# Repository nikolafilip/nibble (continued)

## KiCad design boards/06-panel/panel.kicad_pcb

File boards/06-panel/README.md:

# Board 06: front panel

The test fixture and the face of the machine. 80 transistors, 56 LEDs, 72 resistors.

- **Level switches** (four DIP-8): A3..A0, B3..B0, and the 24 control lines. A closed switch connects the line to +5 V through 10k, so a switch left on can never fight a board that pulls the line low; it only supplies a 1 where nothing else drives.
- **Data switches** (DIP-4): the input port. A closed switch is a 1; while `INP` is high the four bits are driven onto the bus through the usual NAND and open-drain transistor, which is how the IN instruction reads them. To force the bus by hand, close the INP switch too.
- **CLK and RST buttons**: RC debounce, an NMOS Schmitt trigger (two inverters, 1 Meg feedback), 10k and a diode onto the line. One press = one clean edge at every threshold corner (simulated with contact bounce). The clock board can drive the same lines later.
- **1 Meg pull-down** on every switched or observed line, so a line reads 0 when no board drives it.
- **An LED on every line**: 52 bus lines directly, plus the four data bits through inverters so the LED shows the data, not the active-low wire.

First test with hub + panel + ALU: set A, B, SUB, EO on the switches; read the result on the data LEDs and CF/ZF.
Generated by `sim/build_panel.py`. ERC clean; export simulated (`sim/out/panel_sim.cir`).

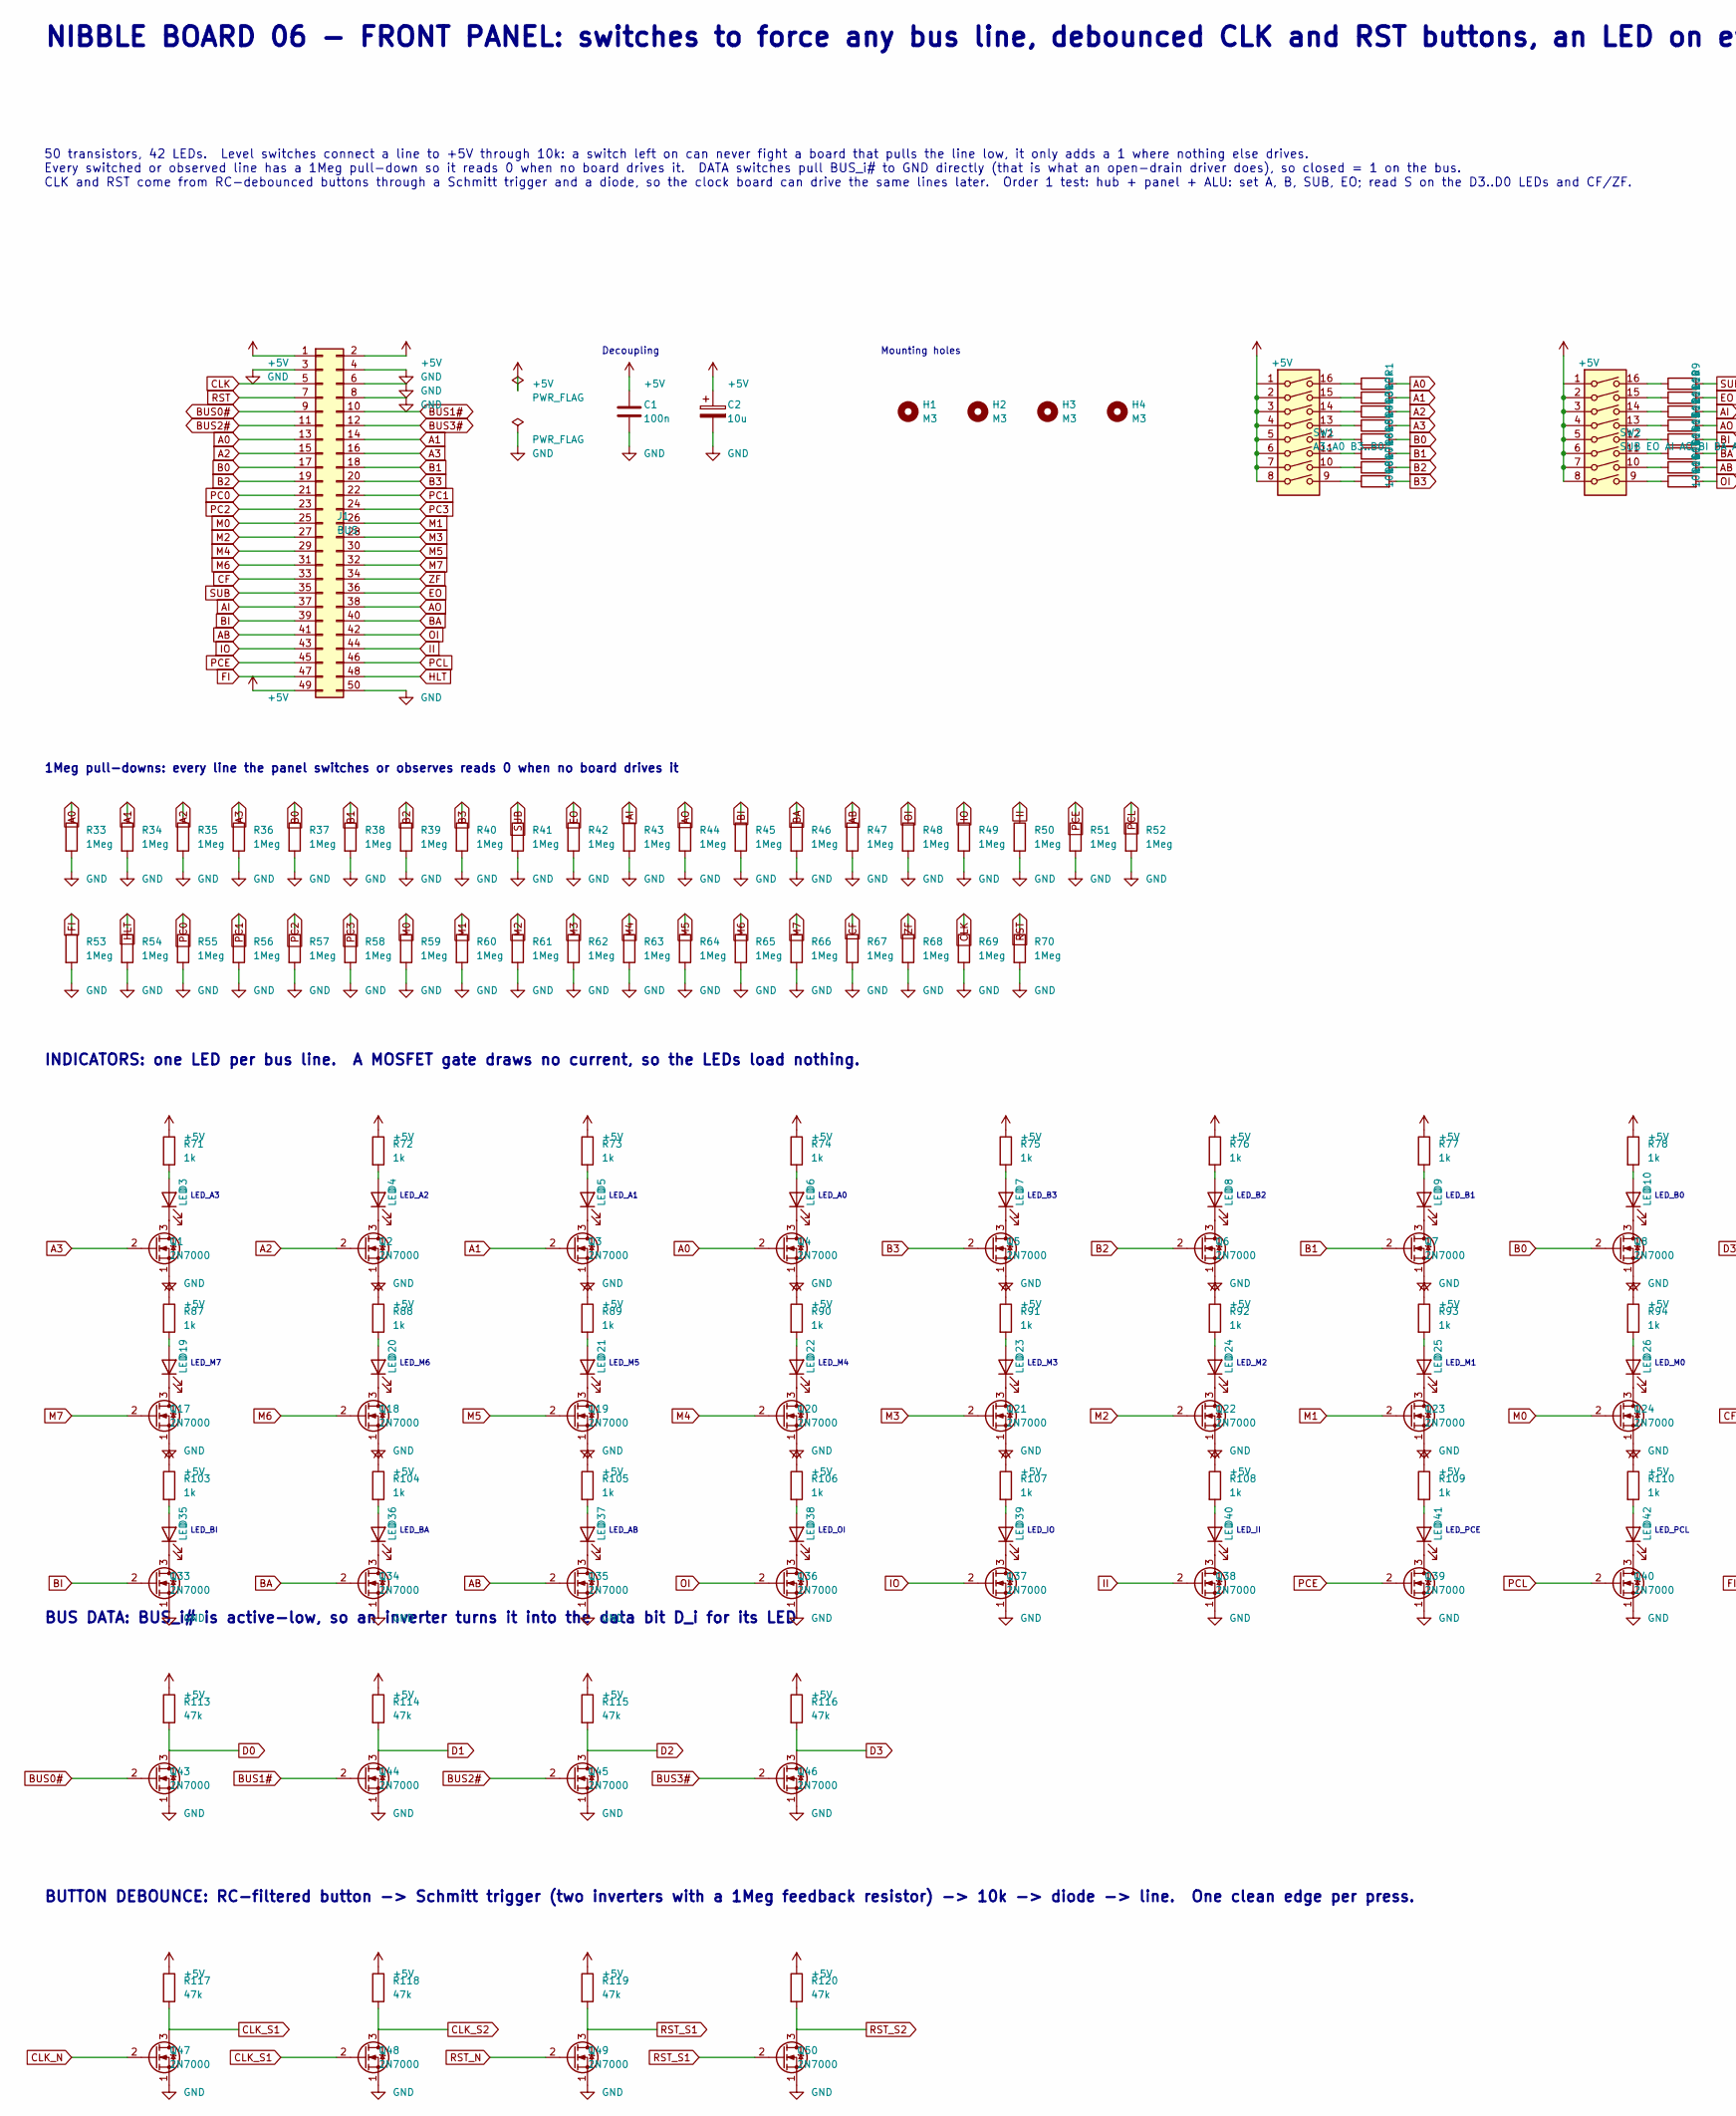
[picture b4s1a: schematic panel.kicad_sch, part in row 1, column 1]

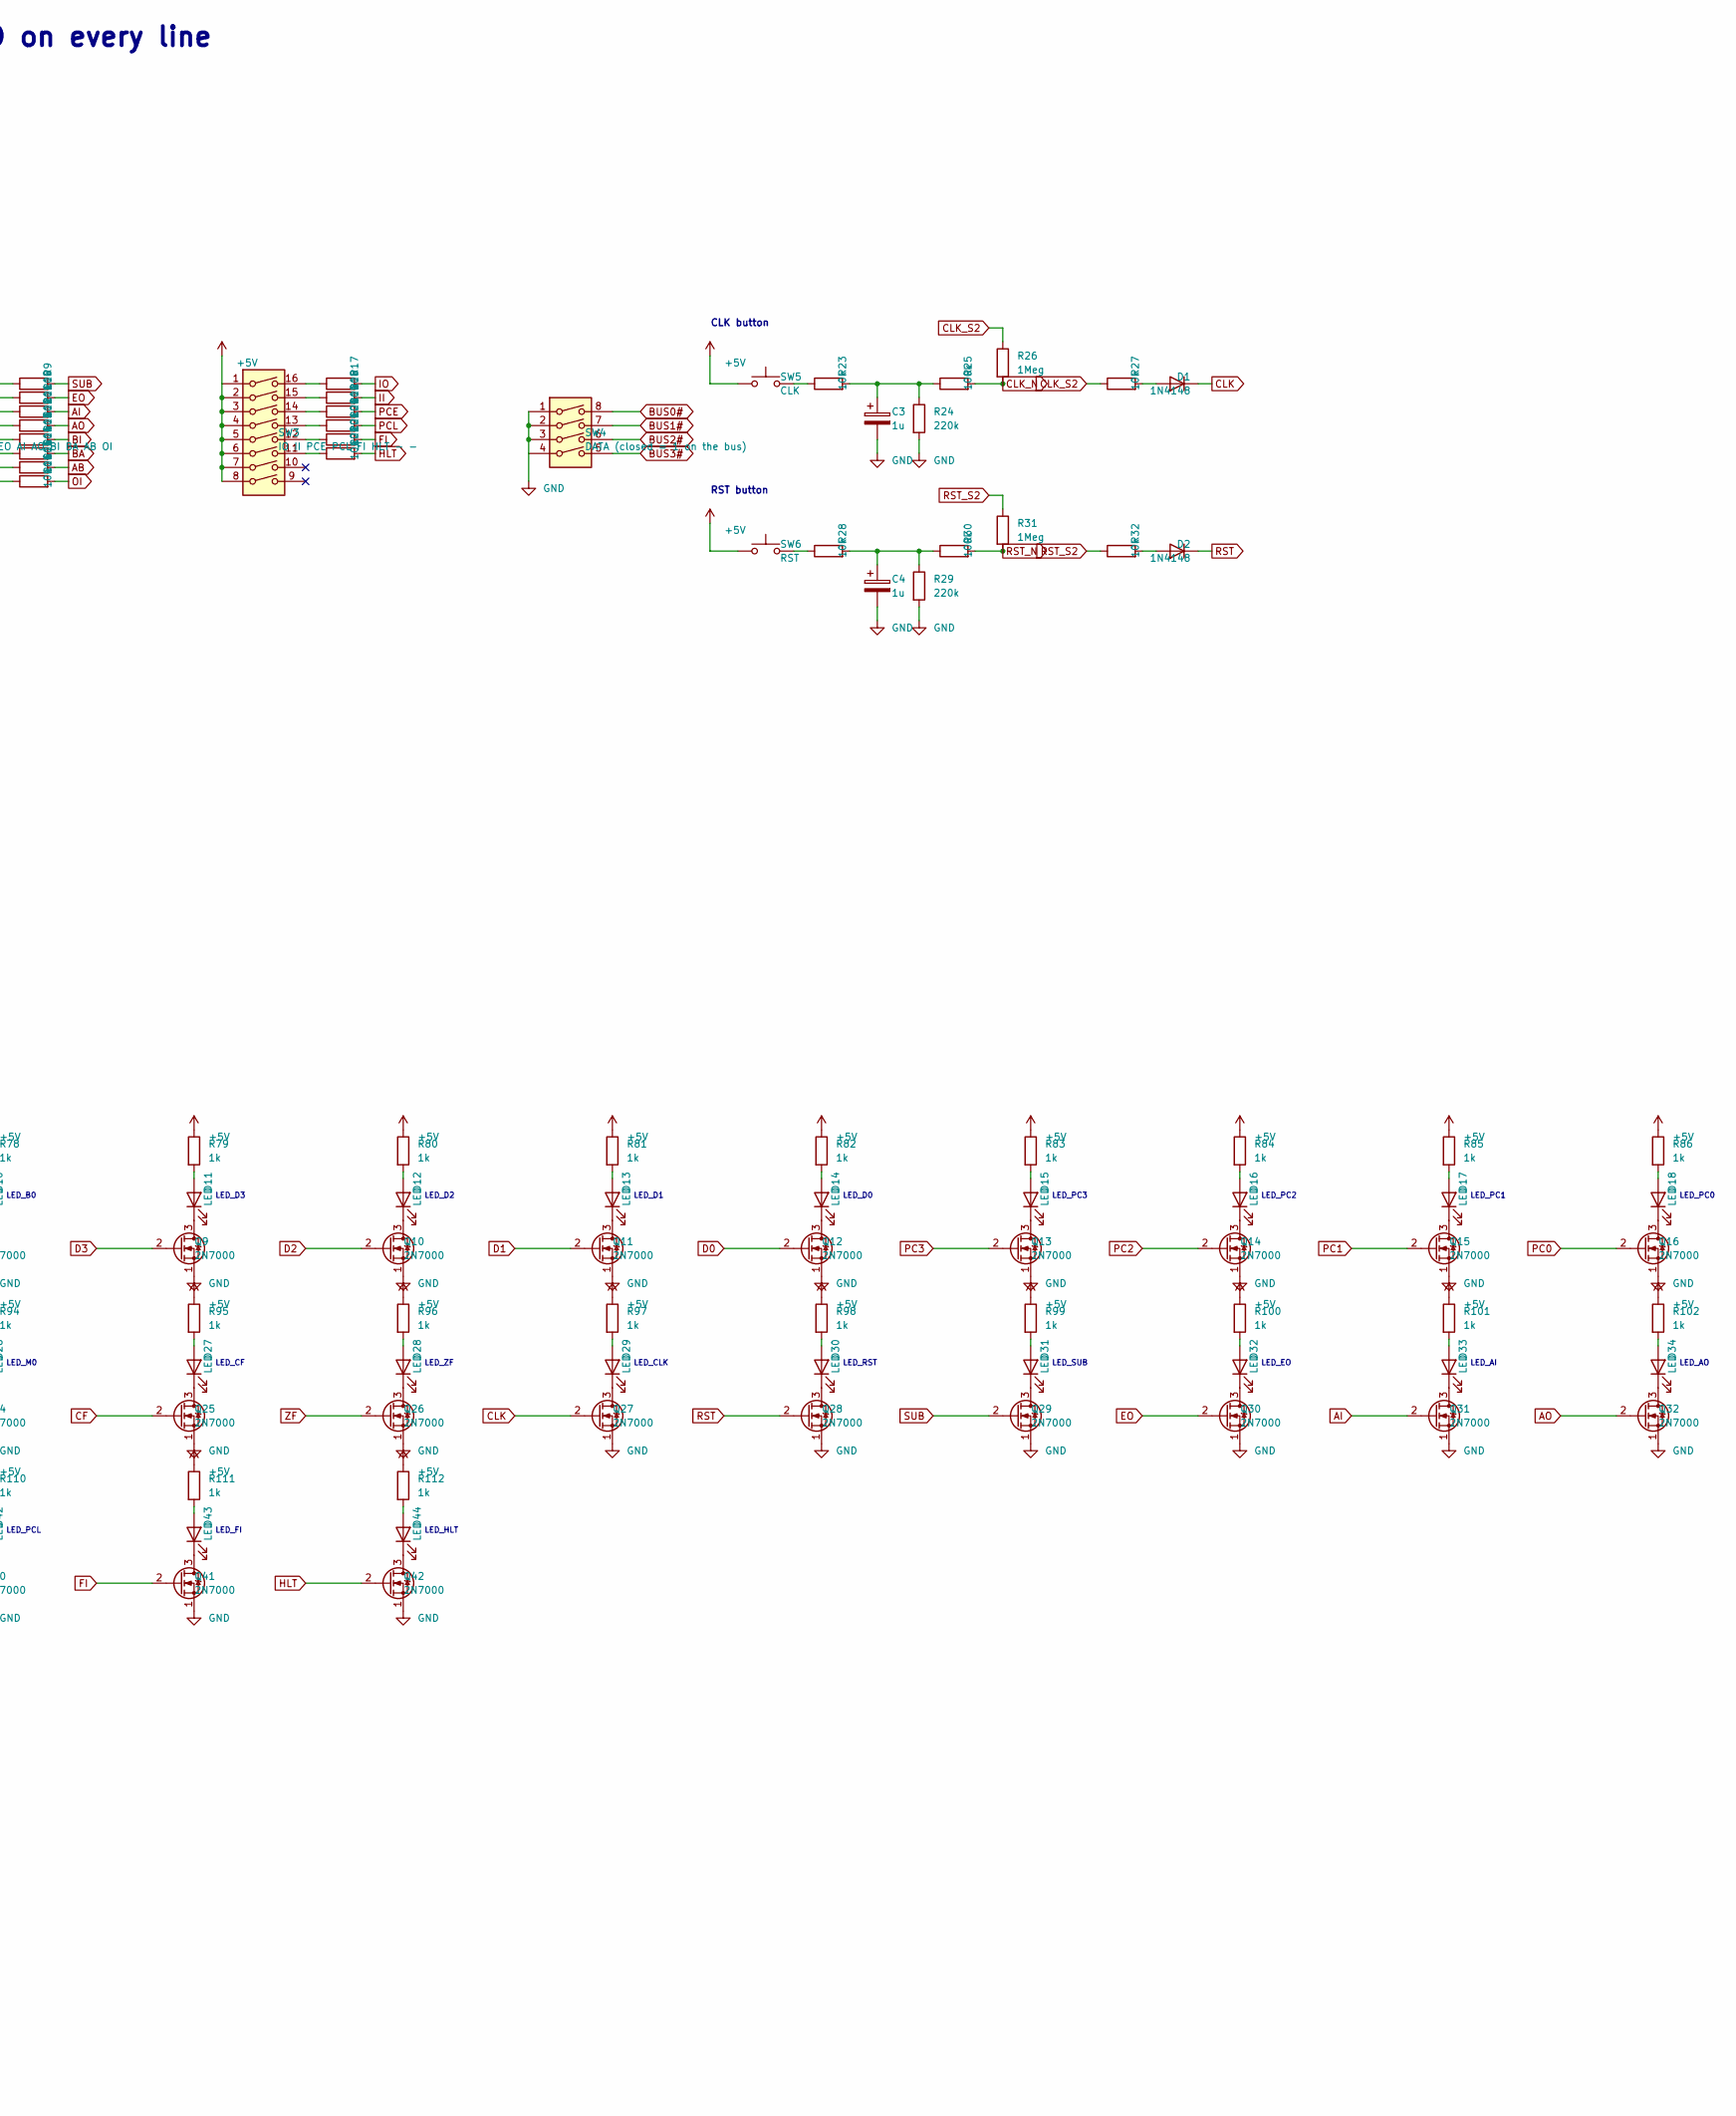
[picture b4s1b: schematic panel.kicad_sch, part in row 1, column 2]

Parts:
C1: 100n; C_Disc_D5.0mm_W2.5mm_P2.50mm
C2: 10u; CP_Radial_D5.0mm_P2.00mm
C3, C4: 1u; CP_Radial_D5.0mm_P2.00mm
D1, D2: 1N4148; D_DO-35_SOD27_P7.62mm_Horizontal
D3, D4, D5, D6, D7, D8, D9, D10, D11, D12, D13, D14, D15, D16, D17, D18, D19, D20, D21, D22, D23, D24, D25, D26, D27, D28, D29, D30, D31, D32, D33, D34, D35, D36, D37, D38, D39, D40, D41, D42, D43, D44: LED; LED_D3.0mm
H1, H2, H3, H4: M3; MountingHole_3.2mm_M3_Pad
J1: BUS; IDC-Header_2x25_P2.54mm_Vertical
Q1, Q2, Q3, Q4, Q5, Q6, Q7, Q8, Q9, Q10, Q11, Q12, Q13, Q14, Q15, Q16, Q17, Q18, Q19, Q20, Q21, Q22, Q23, Q24, Q25, Q26, Q27, Q28, Q29, Q30, Q31, Q32, Q33, Q34, Q35, Q36, Q37, Q38, Q39, Q40, Q41, Q42, Q43, Q44, Q45, Q46, Q47, Q48, Q49, Q50: 2N7000; TO-92_Inline_Wide
R1, R2, R3, R4, R5, R6, R7, R8, R9, R10, R11, R12, R13, R14, R15, R16, R17, R18, R19, R20, R21, R22, R23, R27, R28, R32: 10k; R_Axial_DIN0207_L6.3mm_D2.5mm_P5.08mm_Vertical
R24, R29: 220k; R_Axial_DIN0207_L6.3mm_D2.5mm_P5.08mm_Vertical
R25, R30: 100k; R_Axial_DIN0207_L6.3mm_D2.5mm_P5.08mm_Vertical
R26, R31, R33, R34, R35, R36, R37, R38, R39, R40, R41, R42, R43, R44, R45, R46, R47, R48, R49, R50, R51, R52, R53, R54, R55, R56, R57, R58, R59, R60, R61, R62, R63, R64, R65, R66, R67, R68, R69, R70: 1Meg; R_Axial_DIN0207_L6.3mm_D2.5mm_P5.08mm_Vertical
R71, R72, R73, R74, R75, R76, R77, R78, R79, R80, R81, R82, R83, R84, R85, R86, R87, R88, R89, R90, R91, R92, R93, R94, R95, R96, R97, R98, R99, R100, R101, R102, R103, R104, R105, R106, R107, R108, R109, R110, R111, R112: 1k; R_Axial_DIN0207_L6.3mm_D2.5mm_P5.08mm_Vertical
R113, R114, R115, R116, R117, R118, R119, R120: 47k; R_Axial_DIN0207_L6.3mm_D2.5mm_P5.08mm_Vertical
SW1: A3..A0 B3..B0; SW_DIP_SPSTx08_Slide_9.78x22.5mm_W7.62mm_P2.54mm
SW2: SUB EO AI AO BI BA AB OI; SW_DIP_SPSTx08_Slide_9.78x22.5mm_W7.62mm_P2.54mm
SW3: IO II PCE PCL FI HLT - -; SW_DIP_SPSTx08_Slide_9.78x22.5mm_W7.62mm_P2.54mm
SW4: DATA (closed = 1 on the bus); SW_DIP_SPSTx04_Slide_9.78x12.34mm_W7.62mm_P2.54mm
SW5: CLK; SW_PUSH_6mm
SW6: RST; SW_PUSH_6mm

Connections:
+5V: C1.1, C2.1, J1.1, J1.2, J1.49, R71.1, R72.1, R73.1, R74.1, R75.1, R76.1, R77.1, R78.1, R79.1, R80.1, R81.1, R82.1, R83.1, R84.1, R85.1, R86.1, R87.1, R88.1, R89.1, R90.1, R91.1, R92.1, R93.1, R94.1, R95.1, R96.1, R97.1, R98.1, R99.1, R100.1, R101.1, R102.1, R103.1, R104.1, R105.1, R106.1, R107.1, R108.1, R109.1, R110.1, R111.1, R112.1, R113.1, R114.1, R115.1, R116.1, R117.1, R118.1, R119.1, R120.1, SW1.1, SW1.2, SW1.3, SW1.4, SW1.5, SW1.6, SW1.7, SW1.8, SW2.1, SW2.2, SW2.3, SW2.4, SW2.5, SW2.6, SW2.7, SW2.8, SW3.1, SW3.2, SW3.3, SW3.4, SW3.5, SW3.6, SW3.7, SW3.8, SW5.1, SW6.1
A0: J1.13, Q4.2 (G), R1.2, R33.1
A1: J1.14, Q3.2 (G), R2.2, R34.1
A2: J1.15, Q2.2 (G), R3.2, R35.1
A3: J1.16, Q1.2 (G), R4.2, R36.1
AB: J1.41, Q35.2 (G), R15.2, R47.1
AI: J1.37, Q31.2 (G), R11.2, R43.1
AO: J1.38, Q32.2 (G), R12.2, R44.1
B0: J1.17, Q8.2 (G), R5.2, R37.1
B1: J1.18, Q7.2 (G), R6.2, R38.1
B2: J1.19, Q6.2 (G), R7.2, R39.1
B3: J1.20, Q5.2 (G), R8.2, R40.1
BA: J1.40, Q34.2 (G), R14.2, R46.1
BI: J1.39, Q33.2 (G), R13.2, R45.1
BUS0#: J1.9, Q43.2 (G), SW4.8
BUS1#: J1.10, Q44.2 (G), SW4.7
BUS2#: J1.11, Q45.2 (G), SW4.6
BUS3#: J1.12, Q46.2 (G), SW4.5
CF: J1.33, Q25.2 (G), R67.1
CLK: D1.1 (K), J1.5, Q27.2 (G), R69.1
CLK_N: Q47.2 (G), R25.2, R26.2
CLK_S1: Q47.3 (D), Q48.2 (G), R117.2
CLK_S2: Q48.3 (D), R26.1, R27.1, R118.2
D0: Q12.2 (G), Q43.3 (D), R113.2
D1: Q11.2 (G), Q44.3 (D), R114.2
D2: Q10.2 (G), Q45.3 (D), R115.2
D3: Q9.2 (G), Q46.3 (D), R116.2
EO: J1.36, Q30.2 (G), R10.2, R42.1
FI: J1.47, Q41.2 (G), R21.2, R53.1
GND: C1.2, C2.2, C3.2, C4.2, J1.3, J1.4, J1.6, J1.8, J1.50, Q1.1 (S), Q2.1 (S), Q3.1 (S), Q4.1 (S), Q5.1 (S), Q6.1 (S), Q7.1 (S), Q8.1 (S), Q9.1 (S), Q10.1 (S), Q11.1 (S), Q12.1 (S), Q13.1 (S), Q14.1 (S), Q15.1 (S), Q16.1 (S), Q17.1 (S), Q18.1 (S), Q19.1 (S), Q20.1 (S), Q21.1 (S), Q22.1 (S), Q23.1 (S), Q24.1 (S), Q25.1 (S), Q26.1 (S), Q27.1 (S), Q28.1 (S), Q29.1 (S), Q30.1 (S), Q31.1 (S), Q32.1 (S), Q33.1 (S), Q34.1 (S), Q35.1 (S), Q36.1 (S), Q37.1 (S), Q38.1 (S), Q39.1 (S), Q40.1 (S), Q41.1 (S), Q42.1 (S), Q43.1 (S), Q44.1 (S), Q45.1 (S), Q46.1 (S), Q47.1 (S), Q48.1 (S), Q49.1 (S), Q50.1 (S), R24.2, R29.2, R33.2, R34.2, R35.2, R36.2, R37.2, R38.2, R39.2, R40.2, R41.2, R42.2, R43.2, R44.2, R45.2, R46.2, R47.2, R48.2, R49.2, R50.2, R51.2, R52.2, R53.2, R54.2, R55.2, R56.2, R57.2, R58.2, R59.2, R60.2, R61.2, R62.2, R63.2, R64.2, R65.2, R66.2, R67.2, R68.2, R69.2, R70.2, SW4.1, SW4.2, SW4.3, SW4.4
HLT: J1.48, Q42.2 (G), R22.2, R54.1
II: J1.44, Q38.2 (G), R18.2, R50.1
IO: J1.43, Q37.2 (G), R17.2, R49.1
M0: J1.25, Q24.2 (G), R59.1
M1: J1.26, Q23.2 (G), R60.1
M2: J1.27, Q22.2 (G), R61.1
M3: J1.28, Q21.2 (G), R62.1
M4: J1.29, Q20.2 (G), R63.1
M5: J1.30, Q19.2 (G), R64.1
M6: J1.31, Q18.2 (G), R65.1
M7: J1.32, Q17.2 (G), R66.1
unnamed: C3.1, R23.2, R24.1, R25.1
unnamed: C4.1, R28.2, R29.1, R30.1
unnamed: D1.2 (A), R27.2
unnamed: D2.2 (A), R32.2
unnamed: D3.2 (A), R71.2
unnamed: D3.1 (K), Q1.3 (D)
unnamed: D4.2 (A), R72.2
unnamed: D4.1 (K), Q2.3 (D)
unnamed: D5.2 (A), R73.2
unnamed: D5.1 (K), Q3.3 (D)
unnamed: D6.2 (A), R74.2
unnamed: D6.1 (K), Q4.3 (D)
unnamed: D7.2 (A), R75.2
unnamed: D7.1 (K), Q5.3 (D)
unnamed: D8.2 (A), R76.2
unnamed: D8.1 (K), Q6.3 (D)
unnamed: D9.2 (A), R77.2
unnamed: D9.1 (K), Q7.3 (D)
unnamed: D10.2 (A), R78.2
unnamed: D10.1 (K), Q8.3 (D)
unnamed: D11.2 (A), R79.2
unnamed: D11.1 (K), Q9.3 (D)
unnamed: D12.2 (A), R80.2
unnamed: D12.1 (K), Q10.3 (D)
unnamed: D13.2 (A), R81.2
unnamed: D13.1 (K), Q11.3 (D)
unnamed: D14.2 (A), R82.2
unnamed: D14.1 (K), Q12.3 (D)
unnamed: D15.2 (A), R83.2
unnamed: D15.1 (K), Q13.3 (D)
unnamed: D16.2 (A), R84.2
unnamed: D16.1 (K), Q14.3 (D)
unnamed: D17.2 (A), R85.2
unnamed: D17.1 (K), Q15.3 (D)
unnamed: D18.2 (A), R86.2
unnamed: D18.1 (K), Q16.3 (D)
unnamed: D19.2 (A), R87.2
unnamed: D19.1 (K), Q17.3 (D)
unnamed: D20.2 (A), R88.2
unnamed: D20.1 (K), Q18.3 (D)
unnamed: D21.2 (A), R89.2
unnamed: D21.1 (K), Q19.3 (D)
unnamed: D22.2 (A), R90.2
unnamed: D22.1 (K), Q20.3 (D)
unnamed: D23.2 (A), R91.2
unnamed: D23.1 (K), Q21.3 (D)
unnamed: D24.2 (A), R92.2
unnamed: D24.1 (K), Q22.3 (D)
unnamed: D25.2 (A), R93.2
unnamed: D25.1 (K), Q23.3 (D)
unnamed: D26.2 (A), R94.2
unnamed: D26.1 (K), Q24.3 (D)
unnamed: D27.2 (A), R95.2
unnamed: D27.1 (K), Q25.3 (D)
unnamed: D28.2 (A), R96.2
unnamed: D28.1 (K), Q26.3 (D)
unnamed: D29.2 (A), R97.2
unnamed: D29.1 (K), Q27.3 (D)
unnamed: D30.2 (A), R98.2
unnamed: D30.1 (K), Q28.3 (D)
unnamed: D31.2 (A), R99.2
unnamed: D31.1 (K), Q29.3 (D)
unnamed: D32.2 (A), R100.2
unnamed: D32.1 (K), Q30.3 (D)
unnamed: D33.2 (A), R101.2
unnamed: D33.1 (K), Q31.3 (D)
unnamed: D34.2 (A), R102.2
unnamed: D34.1 (K), Q32.3 (D)
unnamed: D35.2 (A), R103.2
unnamed: D35.1 (K), Q33.3 (D)
unnamed: D36.2 (A), R104.2
unnamed: D36.1 (K), Q34.3 (D)
unnamed: D37.2 (A), R105.2
unnamed: D37.1 (K), Q35.3 (D)
unnamed: D38.2 (A), R106.2
unnamed: D38.1 (K), Q36.3 (D)
unnamed: D39.2 (A), R107.2
unnamed: D39.1 (K), Q37.3 (D)
unnamed: D40.2 (A), R108.2
unnamed: D40.1 (K), Q38.3 (D)
unnamed: D41.2 (A), R109.2
unnamed: D41.1 (K), Q39.3 (D)
unnamed: D42.2 (A), R110.2
unnamed: D42.1 (K), Q40.3 (D)
unnamed: D43.2 (A), R111.2
unnamed: D43.1 (K), Q41.3 (D)
unnamed: D44.2 (A), R112.2
unnamed: D44.1 (K), Q42.3 (D)
unnamed: R1.1, SW1.16
unnamed: R2.1, SW1.15
unnamed: R3.1, SW1.14
unnamed: R4.1, SW1.13
unnamed: R5.1, SW1.12
unnamed: R6.1, SW1.11
unnamed: R7.1, SW1.10
unnamed: R8.1, SW1.9
unnamed: R9.1, SW2.16
unnamed: R10.1, SW2.15
unnamed: R11.1, SW2.14
unnamed: R12.1, SW2.13
unnamed: R13.1, SW2.12
unnamed: R14.1, SW2.11
unnamed: R15.1, SW2.10
unnamed: R16.1, SW2.9
unnamed: R17.1, SW3.16
unnamed: R18.1, SW3.15
unnamed: R19.1, SW3.14
unnamed: R20.1, SW3.13
unnamed: R21.1, SW3.12
unnamed: R22.1, SW3.11
unnamed: R23.1, SW5.2
unnamed: R28.1, SW6.2
OI: J1.42, Q36.2 (G), R16.2, R48.1
PC0: J1.21, Q16.2 (G), R55.1
PC1: J1.22, Q15.2 (G), R56.1
PC2: J1.23, Q14.2 (G), R57.1
PC3: J1.24, Q13.2 (G), R58.1
PCE: J1.45, Q39.2 (G), R19.2, R51.1
PCL: J1.46, Q40.2 (G), R20.2, R52.1
RST: D2.1 (K), J1.7, Q28.2 (G), R70.1
RST_N: Q49.2 (G), R30.2, R31.2
RST_S1: Q49.3 (D), Q50.2 (G), R119.2
RST_S2: Q50.3 (D), R31.1, R32.1, R120.2
SUB: J1.35, Q29.2 (G), R9.2, R41.1
ZF: J1.34, Q26.2 (G), R68.1

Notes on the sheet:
NIBBLE BOARD 06 - FRONT PANEL: switches to force any bus line, debounced CLK and RST buttons, an LED on every line
50 transistors, 42 LEDs. Level switches connect a line to +5V through 10k: a switch left on can never fight a board that pulls the line low, it only adds a 1 where nothing else drives. Every switched or observed line has a 1Meg pull-down so it reads 0 when no board drives it. DATA switches pull BUS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
Decoupling
Mounting holes
CLK button
RST button
1Meg pull-downs: every line the panel switches or observes reads 0 when no board drives it
INDICATORS: one LED per bus line. A MOSFET gate draws no current, so the LEDs load nothing.
LED_A3
LED_A2
LED_A1
LED_A0
LED_B3
LED_B2
LED_B1
LED_B0
LED_D3
LED_D2
LED_D1
LED_D0
LED_PC3
LED_PC2
LED_PC1
LED_PC0
LED_M7
LED_M6
LED_M5
LED_M4
LED_M3
LED_M2
LED_M1
LED_M0
LED_CF
LED_ZF
LED_CLK
LED_RST
LED_SUB
LED_EO
LED_AI
LED_AO

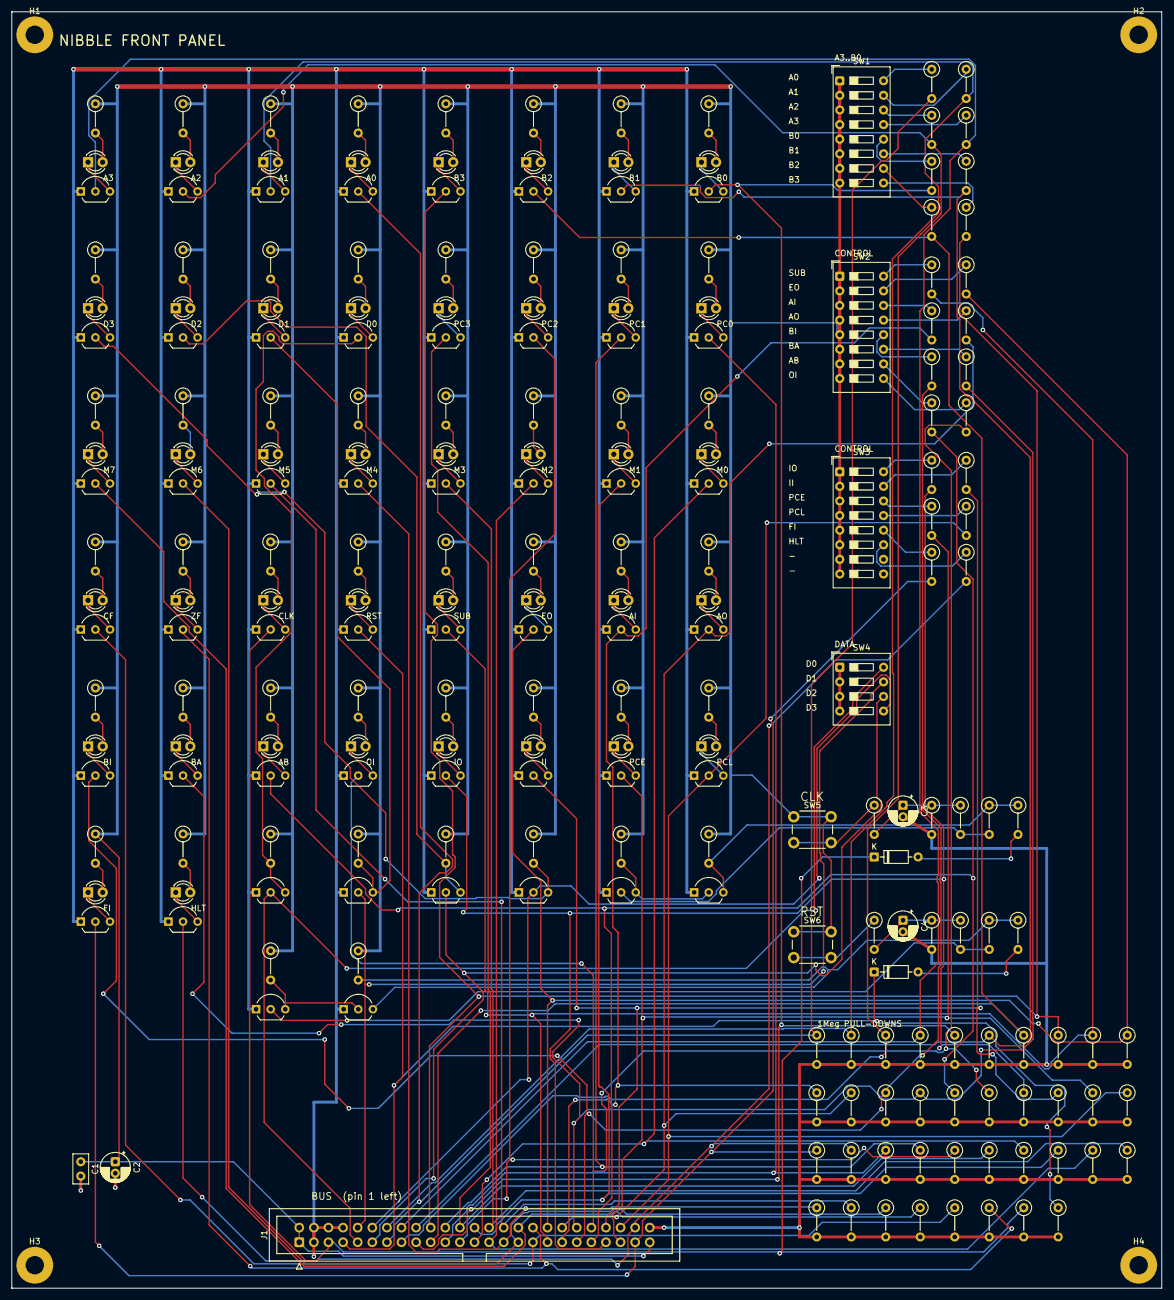
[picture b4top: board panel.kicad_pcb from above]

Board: 2 copper layers, 200.0 x 222.0 mm, 229 parts (0 on the bottom side), 166 nets.

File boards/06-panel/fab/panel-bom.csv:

"Reference","Value","Footprint","QUANTITY"
"C1","100n","Capacitor_THT:C_Disc_D5.0mm_W2.5mm_P2.50mm","1"
"C2","10u","Capacitor_THT:CP_Radial_D5.0mm_P2.00mm","1"
"C3,C4","1u","Capacitor_THT:CP_Radial_D5.0mm_P2.00mm","2"
"D1,D2","1N4148","Diode_THT:D_DO-35_SOD27_P7.62mm_Horizontal","2"
"D3-D44","LED","LED_THT:LED_D3.0mm","42"
"J1","BUS","Connector_IDC:IDC-Header_2x25_P2.54mm_Vertical","1"
"Q1-Q50","2N7000","Package_TO_SOT_THT:TO-92_Inline_Wide","50"
"R1-R23,R27,R28,R32","10k","Resistor_THT:R_Axial_DIN0207_L6.3mm_D2.5mm_P5.08mm_Vertical","26"
"R24,R29","220k","Resistor_THT:R_Axial_DIN0207_L6.3mm_D2.5mm_P5.08mm_Vertical","2"
"R25,R30","100k","Resistor_THT:R_Axial_DIN0207_L6.3mm_D2.5mm_P5.08mm_Vertical","2"
"R26,R31,R33-R70","1Meg","Resistor_THT:R_Axial_DIN0207_L6.3mm_D2.5mm_P5.08mm_Vertical","40"
"R71-R112","1k","Resistor_THT:R_Axial_DIN0207_L6.3mm_D2.5mm_P5.08mm_Vertical","42"
"R113-R120","47k","Resistor_THT:R_Axial_DIN0207_L6.3mm_D2.5mm_P5.08mm_Vertical","8"
"SW1","A3..A0 B3..B0","Button_Switch_THT:SW_DIP_SPSTx08_Slide_9.78x22.5mm_W7.62mm_P2.54mm","1"
"SW2","SUB EO AI AO BI BA AB OI","Button_Switch_THT:SW_DIP_SPSTx08_Slide_9.78x22.5mm_W7.62mm_P2.54mm","1"
"SW3","IO II PCE PCL FI HLT - -","Button_Switch_THT:SW_DIP_SPSTx08_Slide_9.78x22.5mm_W7.62mm_P2.54mm","1"
"SW4","DATA (closed = 1 on the bus)","Button_Switch_THT:SW_DIP_SPSTx04_Slide_9.78x12.34mm_W7.62mm_P2.54mm","1"
"SW5","CLK","Button_Switch_THT:SW_PUSH_6mm","1"
"SW6","RST","Button_Switch_THT:SW_PUSH_6mm","1"

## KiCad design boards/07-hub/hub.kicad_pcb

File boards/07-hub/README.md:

# Board 07: bus hub

No logic. USB-B power entry through a 750 mA polyfuse, a power LED, bulk
capacitance, the four 10k pull-ups for BUS0#..BUS3# (the only pull-ups on the
bus in the whole machine), test loops on the bus, clock and reset lines, and
eight identical 64-pin headers. Every board plugs in with a straight 64-way
ribbon cable. The USB plug is the power switch.

Generated by `sim/build_hub.py`. ERC clean.

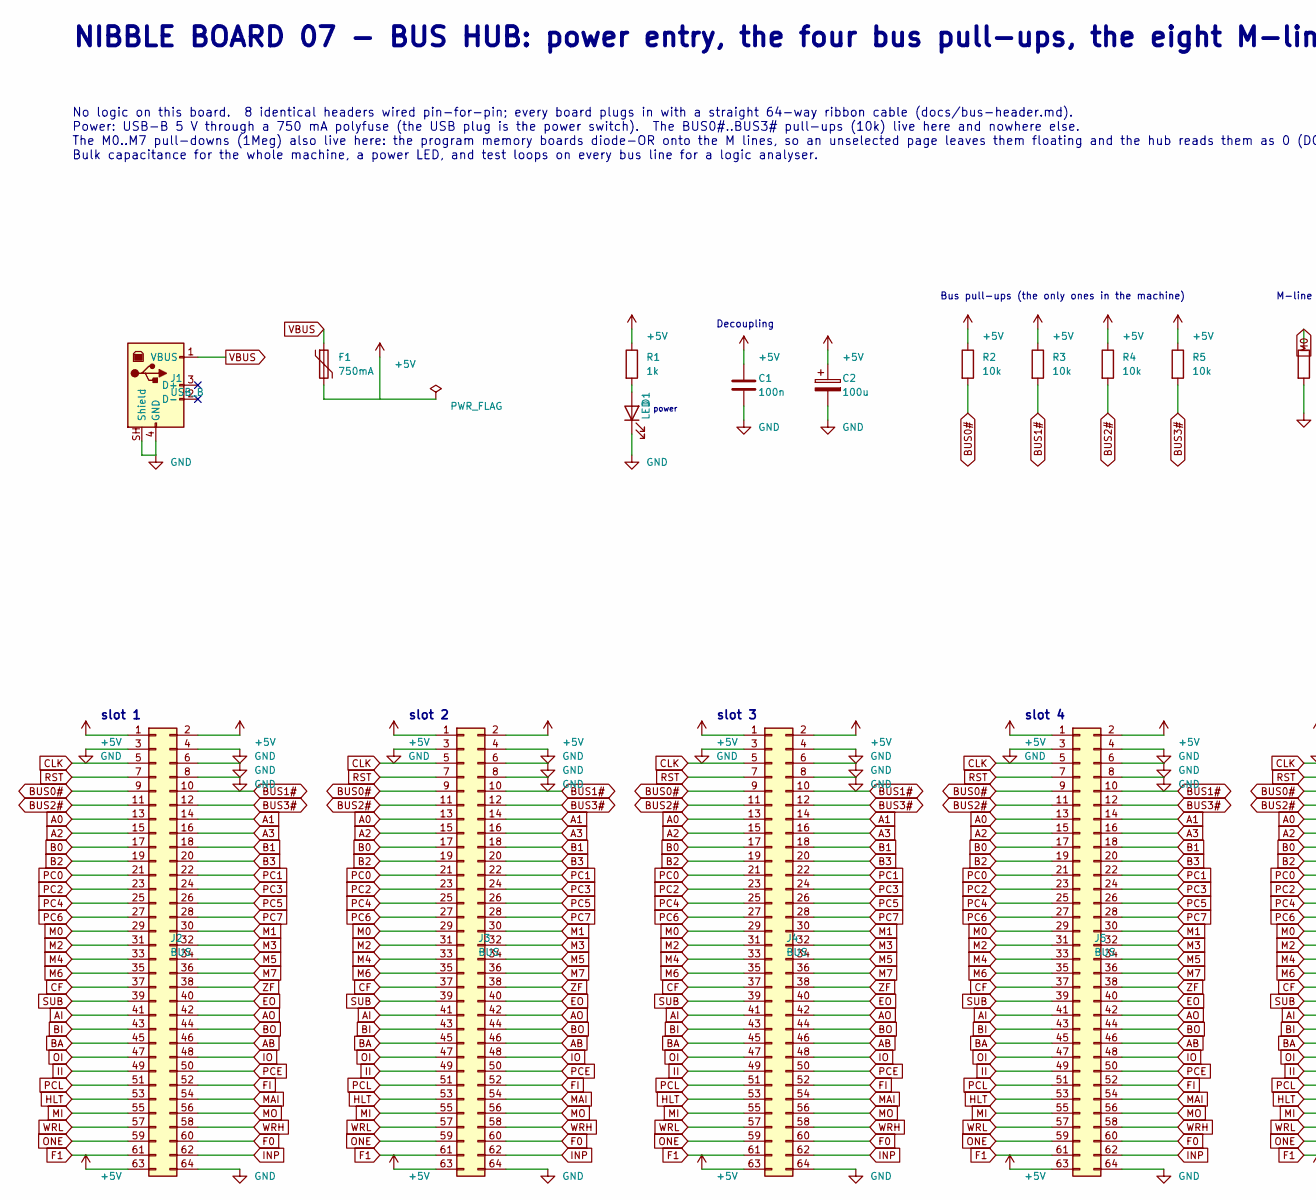
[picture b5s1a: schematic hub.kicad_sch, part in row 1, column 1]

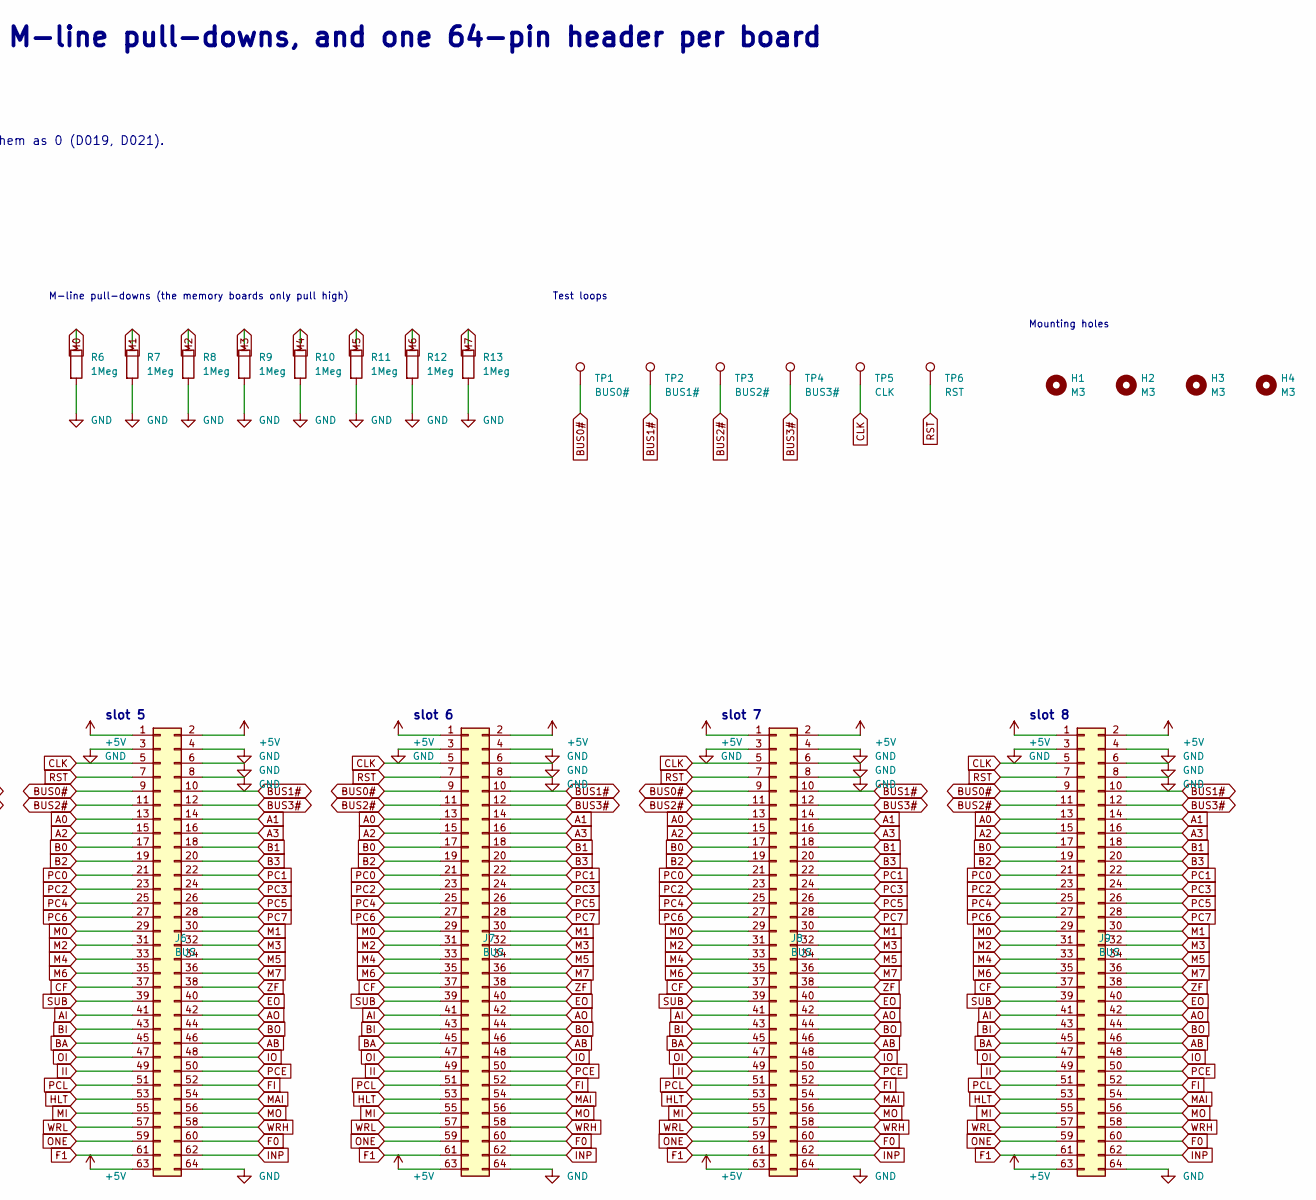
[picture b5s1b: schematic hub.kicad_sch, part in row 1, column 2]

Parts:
C1: 100n; C_Disc_D5.0mm_W2.5mm_P2.50mm
C2: 100u; CP_Radial_D5.0mm_P2.00mm
D1: LED; LED_D3.0mm
F1: 750mA; Fuse_BelFuse_0ZRE0075FF_L11.5mm_W4.8mm
H1, H2, H3, H4: M3; MountingHole_3.2mm_M3_Pad
J1: USB_B; USB_B_OST_USB-B1HSxx_Horizontal
J2, J3, J4, J5, J6, J7, J8, J9: BUS; IDC-Header_2x32_P2.54mm_Vertical
R1: 1k; R_Axial_DIN0207_L6.3mm_D2.5mm_P5.08mm_Vertical
R2, R3, R4, R5: 10k; R_Axial_DIN0207_L6.3mm_D2.5mm_P5.08mm_Vertical
R6, R7, R8, R9, R10, R11, R12, R13: 1Meg; R_Axial_DIN0207_L6.3mm_D2.5mm_P5.08mm_Vertical
TP1: BUS0#; TestPoint_Loop_D2.50mm_Drill1.0mm
TP2: BUS1#; TestPoint_Loop_D2.50mm_Drill1.0mm
TP3: BUS2#; TestPoint_Loop_D2.50mm_Drill1.0mm
TP4: BUS3#; TestPoint_Loop_D2.50mm_Drill1.0mm
TP5: CLK; TestPoint_Loop_D2.50mm_Drill1.0mm
TP6: RST; TestPoint_Loop_D2.50mm_Drill1.0mm

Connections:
+5V: C1.1, C2.1, F1.2, J2.1, J2.2, J2.63, J3.1, J3.2, J3.63, J4.1, J4.2, J4.63, J5.1, J5.2, J5.63, J6.1, J6.2, J6.63, J7.1, J7.2, J7.63, J8.1, J8.2, J8.63, J9.1, J9.2, J9.63, R1.1, R2.1, R3.1, R4.1, R5.1
A0: J2.13, J3.13, J4.13, J5.13, J6.13, J7.13, J8.13, J9.13
A1: J2.14, J3.14, J4.14, J5.14, J6.14, J7.14, J8.14, J9.14
A2: J2.15, J3.15, J4.15, J5.15, J6.15, J7.15, J8.15, J9.15
A3: J2.16, J3.16, J4.16, J5.16, J6.16, J7.16, J8.16, J9.16
AB: J2.46, J3.46, J4.46, J5.46, J6.46, J7.46, J8.46, J9.46
AI: J2.41, J3.41, J4.41, J5.41, J6.41, J7.41, J8.41, J9.41
AO: J2.42, J3.42, J4.42, J5.42, J6.42, J7.42, J8.42, J9.42
B0: J2.17, J3.17, J4.17, J5.17, J6.17, J7.17, J8.17, J9.17
B1: J2.18, J3.18, J4.18, J5.18, J6.18, J7.18, J8.18, J9.18
B2: J2.19, J3.19, J4.19, J5.19, J6.19, J7.19, J8.19, J9.19
B3: J2.20, J3.20, J4.20, J5.20, J6.20, J7.20, J8.20, J9.20
BA: J2.45, J3.45, J4.45, J5.45, J6.45, J7.45, J8.45, J9.45
BI: J2.43, J3.43, J4.43, J5.43, J6.43, J7.43, J8.43, J9.43
BO: J2.44, J3.44, J4.44, J5.44, J6.44, J7.44, J8.44, J9.44
BUS0#: J2.9, J3.9, J4.9, J5.9, J6.9, J7.9, J8.9, J9.9, R2.2, TP1.1
BUS1#: J2.10, J3.10, J4.10, J5.10, J6.10, J7.10, J8.10, J9.10, R3.2, TP2.1
BUS2#: J2.11, J3.11, J4.11, J5.11, J6.11, J7.11, J8.11, J9.11, R4.2, TP3.1
BUS3#: J2.12, J3.12, J4.12, J5.12, J6.12, J7.12, J8.12, J9.12, R5.2, TP4.1
CF: J2.37, J3.37, J4.37, J5.37, J6.37, J7.37, J8.37, J9.37
CLK: J2.5, J3.5, J4.5, J5.5, J6.5, J7.5, J8.5, J9.5, TP5.1
EO: J2.40, J3.40, J4.40, J5.40, J6.40, J7.40, J8.40, J9.40
F0: J2.60, J3.60, J4.60, J5.60, J6.60, J7.60, J8.60, J9.60
F1: J2.61, J3.61, J4.61, J5.61, J6.61, J7.61, J8.61, J9.61
FI: J2.52, J3.52, J4.52, J5.52, J6.52, J7.52, J8.52, J9.52
GND: C1.2, C2.2, D1.1 (K), J1.4 (GND), J1.SH (Shield), J2.3, J2.4, J2.6, J2.8, J2.64, J3.3, J3.4, J3.6, J3.8, J3.64, J4.3, J4.4, J4.6, J4.8, J4.64, J5.3, J5.4, J5.6, J5.8, J5.64, J6.3, J6.4, J6.6, J6.8, J6.64, J7.3, J7.4, J7.6, J7.8, J7.64, J8.3, J8.4, J8.6, J8.8, J8.64, J9.3, J9.4, J9.6, J9.8, J9.64, R6.2, R7.2, R8.2, R9.2, R10.2, R11.2, R12.2, R13.2
HLT: J2.53, J3.53, J4.53, J5.53, J6.53, J7.53, J8.53, J9.53
II: J2.49, J3.49, J4.49, J5.49, J6.49, J7.49, J8.49, J9.49
INP: J2.62, J3.62, J4.62, J5.62, J6.62, J7.62, J8.62, J9.62
IO: J2.48, J3.48, J4.48, J5.48, J6.48, J7.48, J8.48, J9.48
M0: J2.29, J3.29, J4.29, J5.29, J6.29, J7.29, J8.29, J9.29, R6.1
M1: J2.30, J3.30, J4.30, J5.30, J6.30, J7.30, J8.30, J9.30, R7.1
M2: J2.31, J3.31, J4.31, J5.31, J6.31, J7.31, J8.31, J9.31, R8.1
M3: J2.32, J3.32, J4.32, J5.32, J6.32, J7.32, J8.32, J9.32, R9.1
M4: J2.33, J3.33, J4.33, J5.33, J6.33, J7.33, J8.33, J9.33, R10.1
M5: J2.34, J3.34, J4.34, J5.34, J6.34, J7.34, J8.34, J9.34, R11.1
M6: J2.35, J3.35, J4.35, J5.35, J6.35, J7.35, J8.35, J9.35, R12.1
M7: J2.36, J3.36, J4.36, J5.36, J6.36, J7.36, J8.36, J9.36, R13.1
MAI: J2.54, J3.54, J4.54, J5.54, J6.54, J7.54, J8.54, J9.54
MI: J2.55, J3.55, J4.55, J5.55, J6.55, J7.55, J8.55, J9.55
MO: J2.56, J3.56, J4.56, J5.56, J6.56, J7.56, J8.56, J9.56
unnamed: D1.2 (A), R1.2
OI: J2.47, J3.47, J4.47, J5.47, J6.47, J7.47, J8.47, J9.47
ONE: J2.59, J3.59, J4.59, J5.59, J6.59, J7.59, J8.59, J9.59
PC0: J2.21, J3.21, J4.21, J5.21, J6.21, J7.21, J8.21, J9.21
PC1: J2.22, J3.22, J4.22, J5.22, J6.22, J7.22, J8.22, J9.22
PC2: J2.23, J3.23, J4.23, J5.23, J6.23, J7.23, J8.23, J9.23
PC3: J2.24, J3.24, J4.24, J5.24, J6.24, J7.24, J8.24, J9.24
PC4: J2.25, J3.25, J4.25, J5.25, J6.25, J7.25, J8.25, J9.25
PC5: J2.26, J3.26, J4.26, J5.26, J6.26, J7.26, J8.26, J9.26
PC6: J2.27, J3.27, J4.27, J5.27, J6.27, J7.27, J8.27, J9.27
PC7: J2.28, J3.28, J4.28, J5.28, J6.28, J7.28, J8.28, J9.28
PCE: J2.50, J3.50, J4.50, J5.50, J6.50, J7.50, J8.50, J9.50
PCL: J2.51, J3.51, J4.51, J5.51, J6.51, J7.51, J8.51, J9.51
RST: J2.7, J3.7, J4.7, J5.7, J6.7, J7.7, J8.7, J9.7, TP6.1
SUB: J2.39, J3.39, J4.39, J5.39, J6.39, J7.39, J8.39, J9.39
VBUS: F1.1, J1.1 (VBUS)
WRH: J2.58, J3.58, J4.58, J5.58, J6.58, J7.58, J8.58, J9.58
WRL: J2.57, J3.57, J4.57, J5.57, J6.57, J7.57, J8.57, J9.57
ZF: J2.38, J3.38, J4.38, J5.38, J6.38, J7.38, J8.38, J9.38

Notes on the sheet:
NIBBLE BOARD 07 - BUS HUB: power entry, the four bus pull-ups, the eight M-line pull-downs, and one 64-pin header per board
No logic on this board. 8 identical headers wired pin-for-pin; every board plugs in with a straight 64-way ribbon cable (docs/bus-header.md). Power: USB-B 5 V through a 750 mA polyfuse (the USB plug is the power switch). The BUS0#..BUS3# pull-ups (10k) live here and nowhere else. The M0..M7 pull-do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
power
Decoupling
Bus pull-ups (the only ones in the machine)
M-line pull-downs (the memory boards only pull high)
Test loops
Mounting holes
slot 1
slot 2
slot 3
slot 4
slot 5
slot 6
slot 7
slot 8
